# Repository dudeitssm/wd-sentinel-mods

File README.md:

WD Sentinel NAS related mods and custom PCBs
---

Contains custom PCBs, mods, etc, relating to the WD Sentinel DX4000 NAS.

How to get started?

1. Download the KiCAD archives (zip files)
2. Unarchive the zips
3. Use OSHPark or any fabhouse to print out the ".kicad_pcb" PCBs

Shoot me an email or open an issue if you have questions: moltensolderlabs AT pm.me

Everything licensed as CC0. Do whatever you want with these files.

Enjoy! Other projects are available on my site: moltensolderlabs.com

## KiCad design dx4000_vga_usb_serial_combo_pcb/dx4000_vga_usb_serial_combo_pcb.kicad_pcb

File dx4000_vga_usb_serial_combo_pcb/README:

* This is a combo PCB that provides serial console, VGA, and dual USB2.0 support to the WD Sentinel DX4000.
--> a 12 pin FFC cable plugs into the USB backpack PCB.
--> a 12 pin FFC cable plugs into the VGA packpack PCB.
--> a 4 pin JST cable plugs into the serial port, located at the front of the DX4000 motherboard.
--> WARNING: you MUST use the same-side-up facing FFC cable, or you can short the USB or VGA.

===

If ya liked this project, or have an improvement in mind, send me an email at moltensolderlabs AT pm.me

Cherish your little Sentinel! I love mine <3

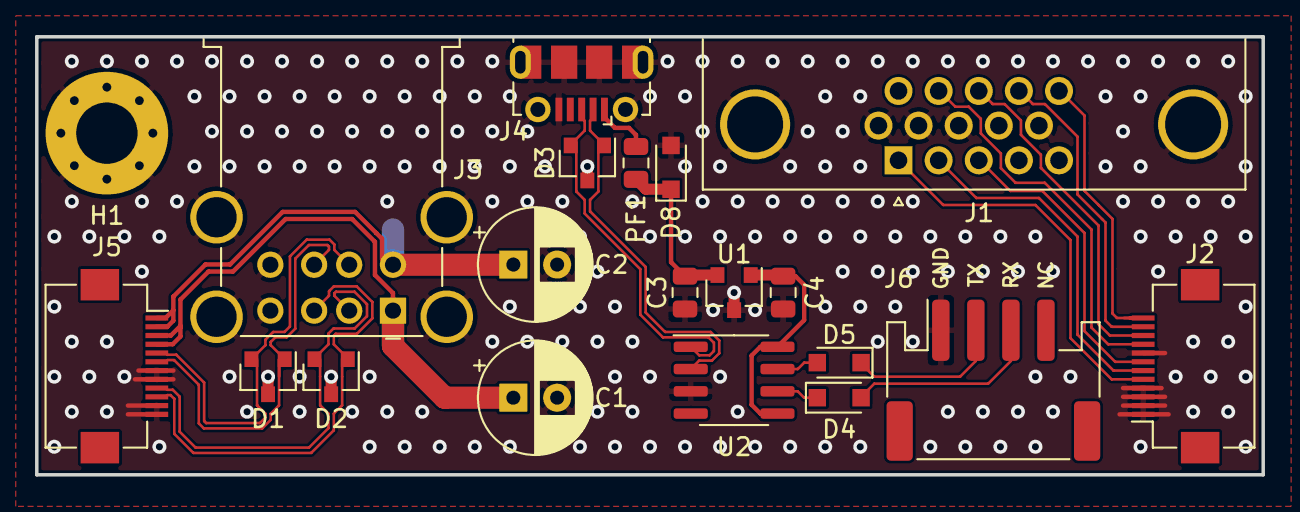
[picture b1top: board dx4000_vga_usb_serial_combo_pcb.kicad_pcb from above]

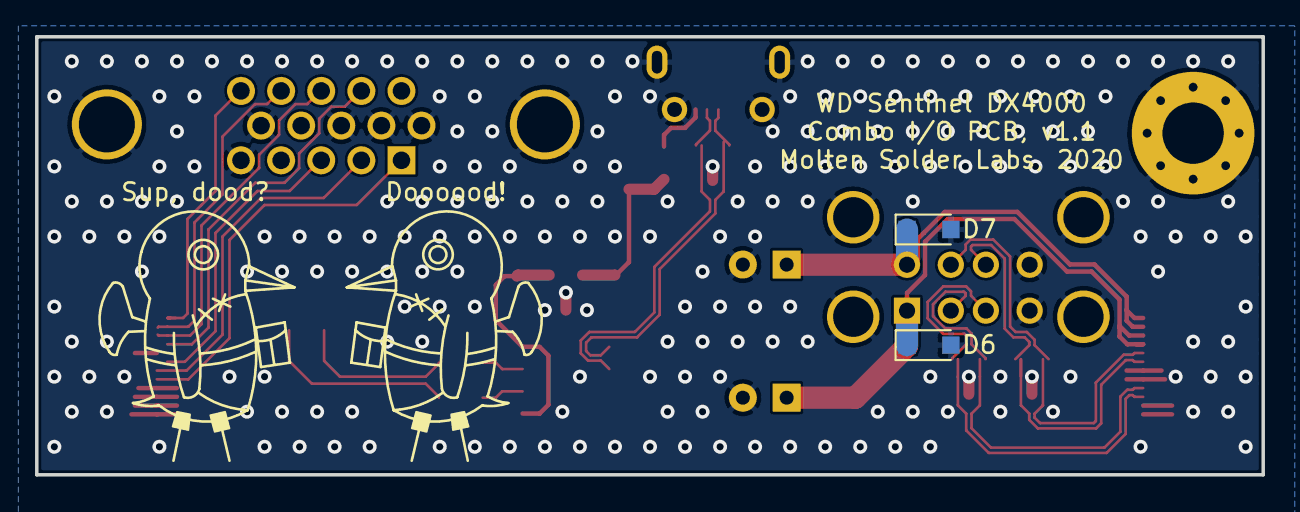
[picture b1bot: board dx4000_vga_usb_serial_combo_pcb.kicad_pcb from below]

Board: 2 copper layers, 70.0 x 25.0 mm, 22 parts (2 on the bottom side), 23 nets.

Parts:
C1, C2: 220u; CP_Radial_D6.3mm_P2.50mm
C3, C4: 10u; C_0805_2012Metric
D1, D2, D3: SESLC5V; SOT-23
D4, D5: NSR0320; D_SOD-323_HandSoldering
D6, D7, D8: GSESLC5V; D_SOD-323_HandSoldering
H1: Keystone_633; MountingHole_3.5mm_Pad_Via
J1: VGA_OUTPUT; DSUB-15-HD_Female_Horizontal_P2.29x1.98mm_EdgePinOffset3.03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
J2: FFC_VGA; Hirose_FH12-12S-0.5SH_1x12-1MP_P0.50mm_Horizontal
J3: Dual_USB; USB_A_Wuerth_61400826021_Horizontal_Stacked
J4: USB_B_Micro; USB_Micro-B_Molex-105017-0001
J5: FFC_USB; Hirose_FH12-12S-0.5SH_1x12-1MP_P0.50mm_Horizontal
J6: TO_DX_SER_HDR; JST_PH_S4B-PH-SM4-TB_1x04-1MP_P2.00mm_Horizontal
PF1: 0805L010YR; R_0805_2012Metric
U1: MCP1811AT-033; SOT-23
U2: CH330N; SOIC-8_3.9x4.9mm_P1.27mm

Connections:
+3V3: C4.1, U1.1, U2.5, U2.8
/5V_A: C2.1, D7.1, J3.5, J5.1, J5.2
/5V_B: C1.1, D6.1, J3.1, J5.3, J5.4
/5V_C: C3.1, D8.1, PF1.1, U1.2
/BLU_VID: J1.3, J2.7
/DX_RX: D4.2, J6.3
/DX_TX: D5.1, J6.2
/GRN_VID: J1.2, J2.6
/HSYNC: J1.13, J2.10
/RED_VID: J1.1, J2.5
/SCL: J1.15, J2.12
/SDA: J1.12, J2.9
/UD+: D3.2, J4.3, U2.1
/UD-: D3.1, J4.2, U2.2
/USB_A+: D1.1, J3.7, J5.6
/USB_A-: D1.2, J3.6, J5.5
/USB_B+: D2.1, J3.3, J5.10
/USB_B-: D2.2, J3.2, J5.9
/VSYNC: J1.14, J2.11
GND: C1.2, C2.2, C3.2, C4.2, D1.3, D2.3, D3.3, D6.2, D7.2, D8.2, H1.1, J1.0, J1.5, J1.6, J1.7, J1.8, J1.10, J2.1, J2.2, J2.3, J2.4, J2.8, J3.4, J3.8, J3.9, J4.5, J4.6, J5.7, J5.8, J5.11, J5.12, J6.1, U1.3, U2.3
unnamed: D4.1, U2.6
unnamed: D5.2, U2.7
unnamed: J4.1, PF1.2

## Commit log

2020-12-12 Completely forgot about this project. Enjoy!
    All these files were sitting around, unsorted, since the beginning of the year (when I finished most of them).
    I took some time today to sort everything out. Hope you find these useful.
